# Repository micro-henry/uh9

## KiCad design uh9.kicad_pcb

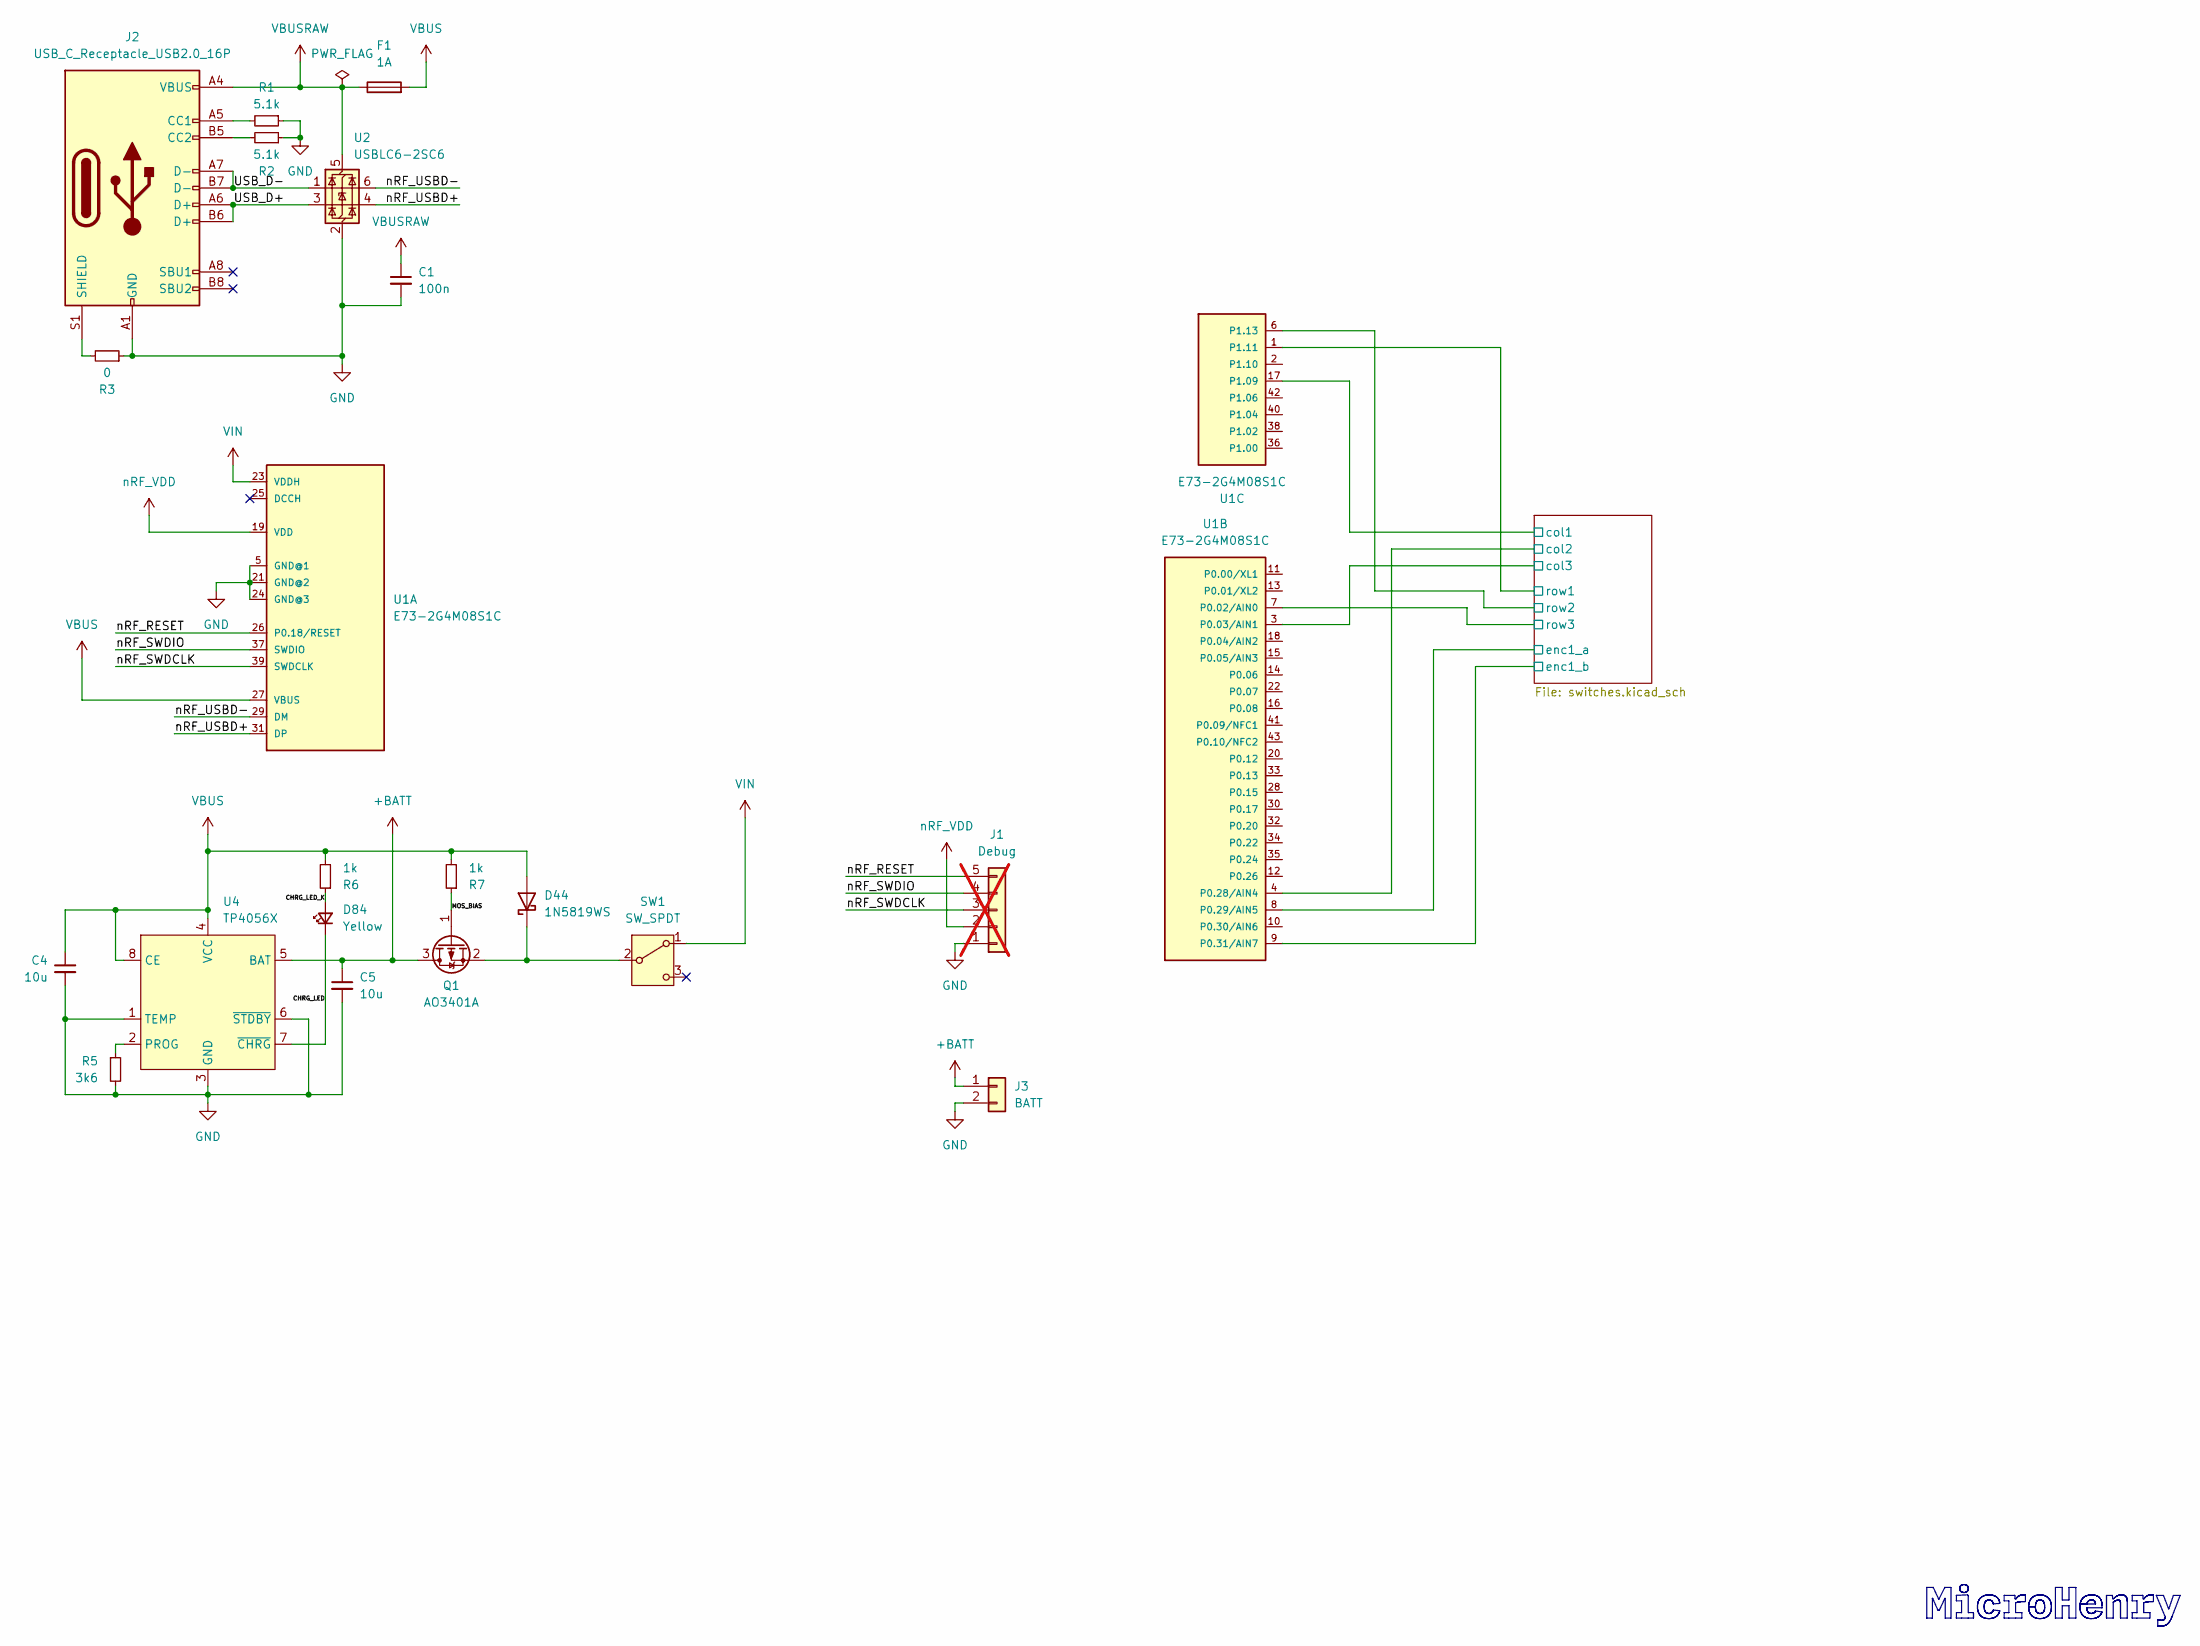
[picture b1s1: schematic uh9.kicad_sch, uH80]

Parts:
C1: 100n; C_0805_2012Metric
C4, C5: 10u; C_0805_2012Metric
D44: 1N5819WS; D_SOD-323
D84: Yellow; LED_0805_2012Metric
F1: 1A; Fuse_0805_2012Metric
J1: Debug; PinHeader_1x05_P2.00mm_Vertical; not fitted
J2: USB_C_Receptacle_USB2.0_16P; USB_C_Receptacle_HRO_TYPE-C-31-M-12
J3: BATT; CONN-SMD_2P-P2.54_MEGASTAR_ZX-XH2.54-2PWT
Q1: AO3401A; SOT-23
R1, R2: 5.1k; R_0805_2012Metric
R3: 0; R_0805_2012Metric
R5: 3k6; R_0805_2012Metric
R6, R7: 1k; R_0805_2012Metric
SW1: SW_SPDT; SW-SMD_3P-P1.50_L2.7-W6.6
U1: E73-2G4M08S1C
U2: USBLC6-2SC6; SOT-23-6
U4: TP4056X; Infineon_PG-DSO-8-27_3.9x4.9mm_EP2.65x3mm_ThermalVias

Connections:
+BATT: C5.1, J3.1, Q1.3 (D), U4.5 (BAT)
/CHRG_LED: D84.1 (K), U4.7 (~CHRG)
/CHRG_LED_K: D84.2 (A), R6.1
/MOS_BIAS: Q1.1 (G), R7.1
/USB_D+: J2.A6 (D+), J2.B6 (D+), U2.3 (I/O2)
/USB_D-: J2.A7 (D-), J2.B7 (D-), U2.1 (I/O1)
/nRF_RESET: J1.5, U1.26 (P0.18/RESET)
/nRF_SWDCLK: J1.3, U1.39 (SWDCLK)
/nRF_SWDIO: J1.4, U1.37 (SWDIO)
/nRF_USBD+: U1.31 (DP), U2.4 (I/O2)
/nRF_USBD-: U1.29 (DM), U2.6 (I/O1)
/switches/col1: U1.17 (P1.09); also elsewhere on the board
/switches/col2: U1.4 (P0.28/AIN4); also elsewhere on the board
/switches/col3: U1.3 (P0.03/AIN1); also elsewhere on the board
/switches/enc1_a: U1.8 (P0.29/AIN5); also elsewhere on the board
/switches/enc1_b: U1.9 (P0.31/AIN7); also elsewhere on the board
/switches/row1: U1.1 (P1.11); also elsewhere on the board
/switches/row2: U1.6 (P1.13); also elsewhere on the board
/switches/row3: U1.7 (P0.02/AIN0); also elsewhere on the board
GND: C1.2, C4.2, C5.2, J1.1, J2.A1 (GND), J2.A12 (GND), J2.B1 (GND), J2.B12 (GND), J3.2, R1.1, R2.1, R3.1, R5.2, U1.5 (GND@1), U1.21 (GND@2), U1.24 (GND@3), U2.2 (GND), U4.1 (TEMP), U4.3 (GND), U4.6 (~STDBY), U4.9 (GND); also elsewhere on the board
unnamed: D44.1 (K), Q1.2 (S), SW1.2 (B)
unnamed: J2.A5 (CC1), R1.2
unnamed: J2.B5 (CC2), R2.2
unnamed: J2.S1 (SHIELD), R3.2
unnamed: R5.1, U4.2 (PROG)
VBUS: C4.1, D44.2 (A), F1.2, R6.2, R7.2, U1.27 (VBUS), U4.4 (VCC), U4.8 (CE)
VBUSRAW: C1.1, F1.1, J2.A4 (VBUS), J2.A9 (VBUS), J2.B4 (VBUS), J2.B9 (VBUS), U2.5 (VBUS)
VIN: SW1.1 (A), U1.23 (VDDH)
nRF_VDD: J1.2, U1.19 (VDD)

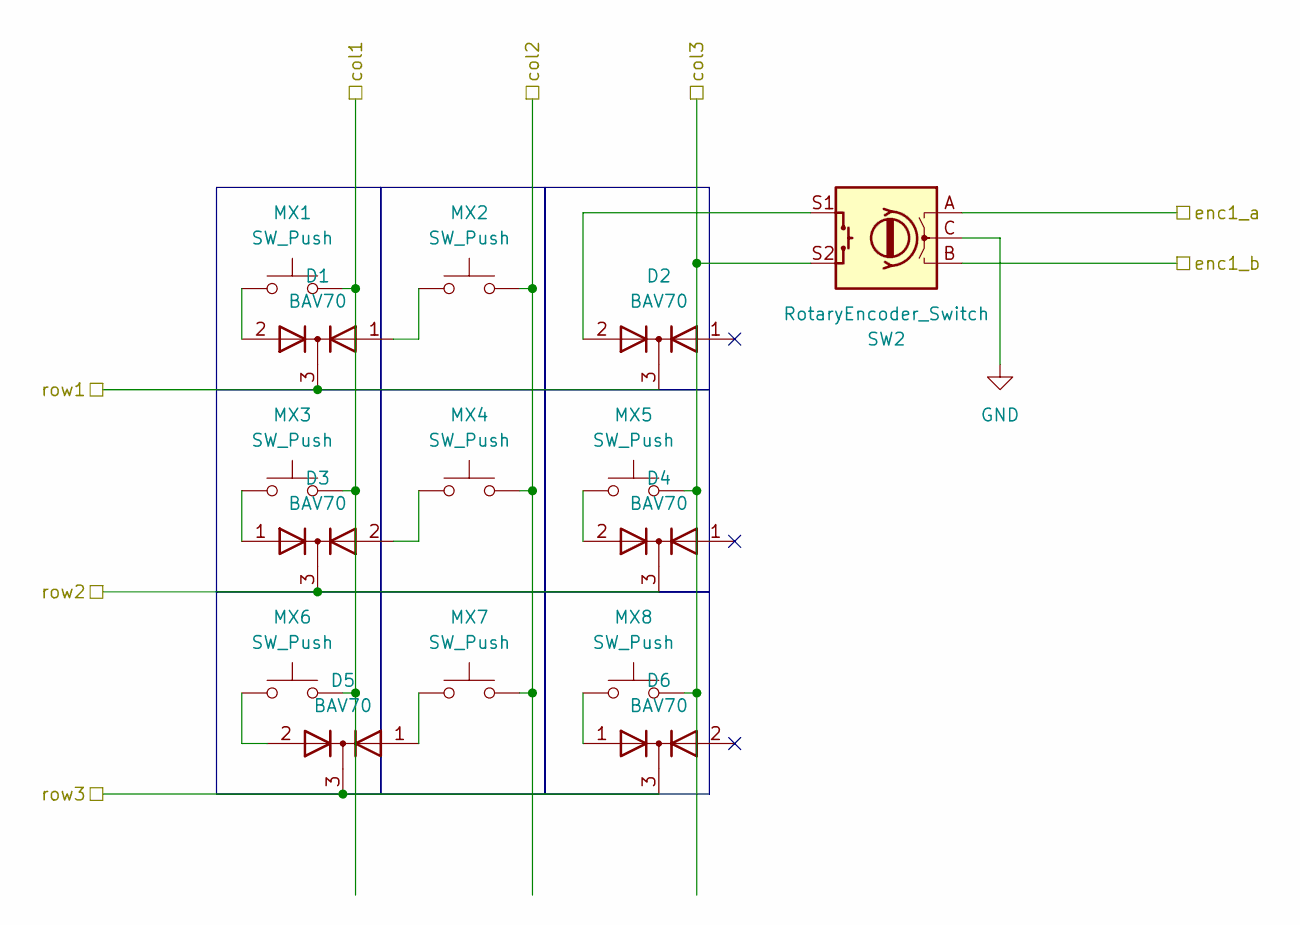
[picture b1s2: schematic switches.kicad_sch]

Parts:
D1, D2, D3, D4, D5, D6: BAV70; SOT-23
MX1, MX2, MX3, MX4, MX5, MX6, MX7, MX8: SW_Push; SW_Hotswap_Kailh_MX_1.00u
SW2: RotaryEncoder_Switch; RotaryEncoder_Alps_EC11E-Switch_Vertical_H20mm

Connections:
/switches/col1: MX1.1, MX3.2, MX6.1; also elsewhere on the board
/switches/col2: MX2.2, MX4.1, MX7.2; also elsewhere on the board
/switches/col3: MX5.1, MX8.2, SW2.S2; also elsewhere on the board
/switches/enc1_a: SW2.A; also elsewhere on the board
/switches/enc1_b: SW2.B; also elsewhere on the board
/switches/row1: D1.3 (K), D2.3 (K); also elsewhere on the board
/switches/row2: D3.3 (K), D4.3 (K); also elsewhere on the board
/switches/row3: D5.3 (K), D6.3 (K); also elsewhere on the board
GND: SW2.C; also elsewhere on the board
unnamed: D1.1 (A), MX2.1
unnamed: D1.2 (A), MX1.2
unnamed: D2.2 (A), SW2.S1
unnamed: D3.1 (A), MX3.1
unnamed: D3.2 (A), MX4.2
unnamed: D4.2 (A), MX5.2
unnamed: D5.1 (A), MX7.1
unnamed: D5.2 (A), MX6.2
unnamed: D6.1 (A), MX8.1

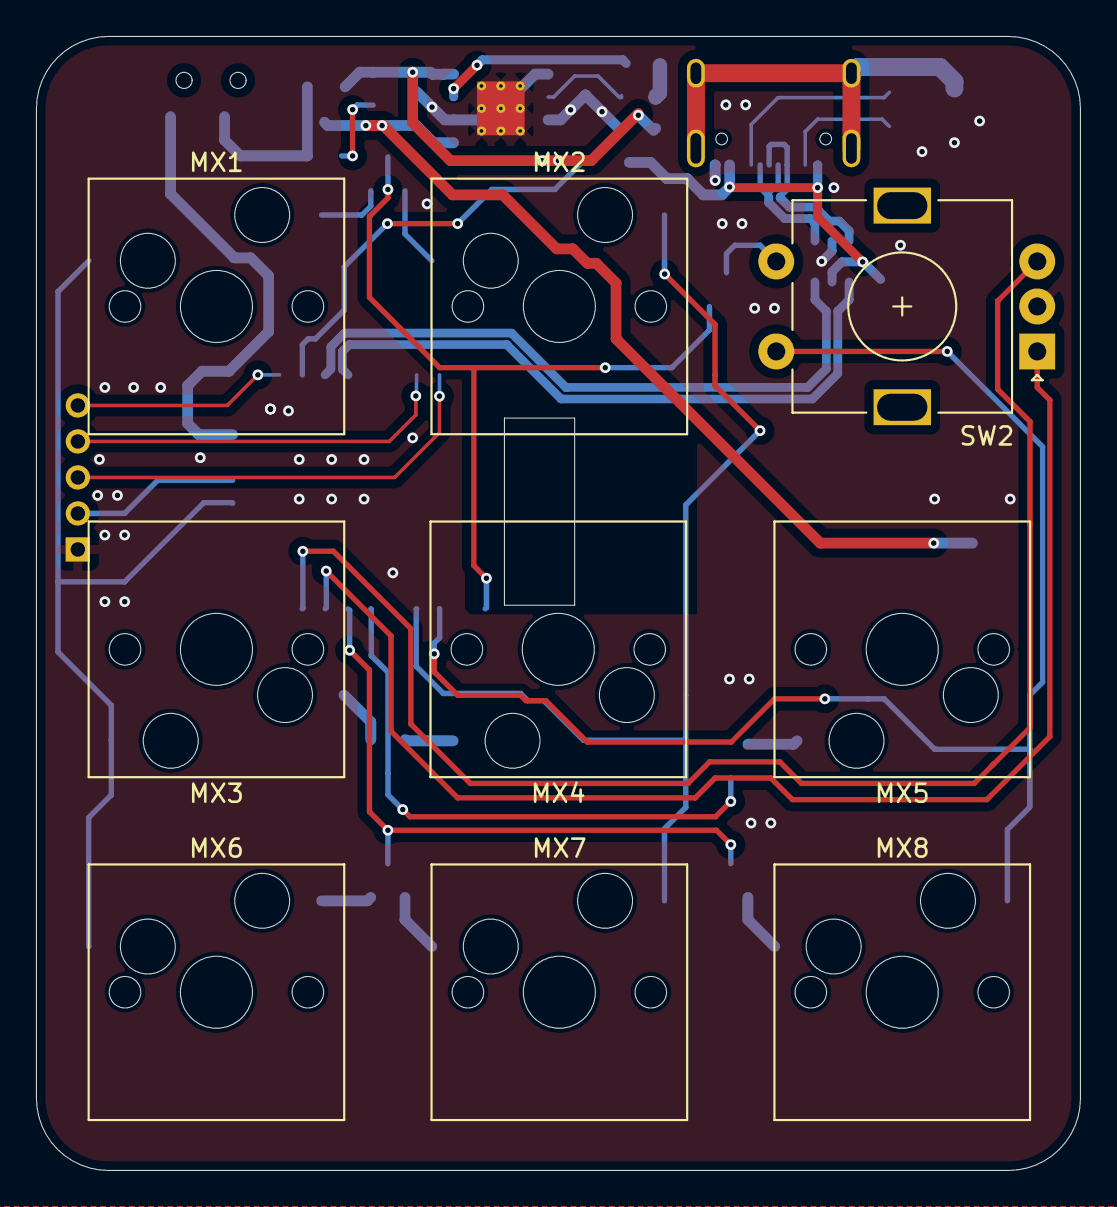
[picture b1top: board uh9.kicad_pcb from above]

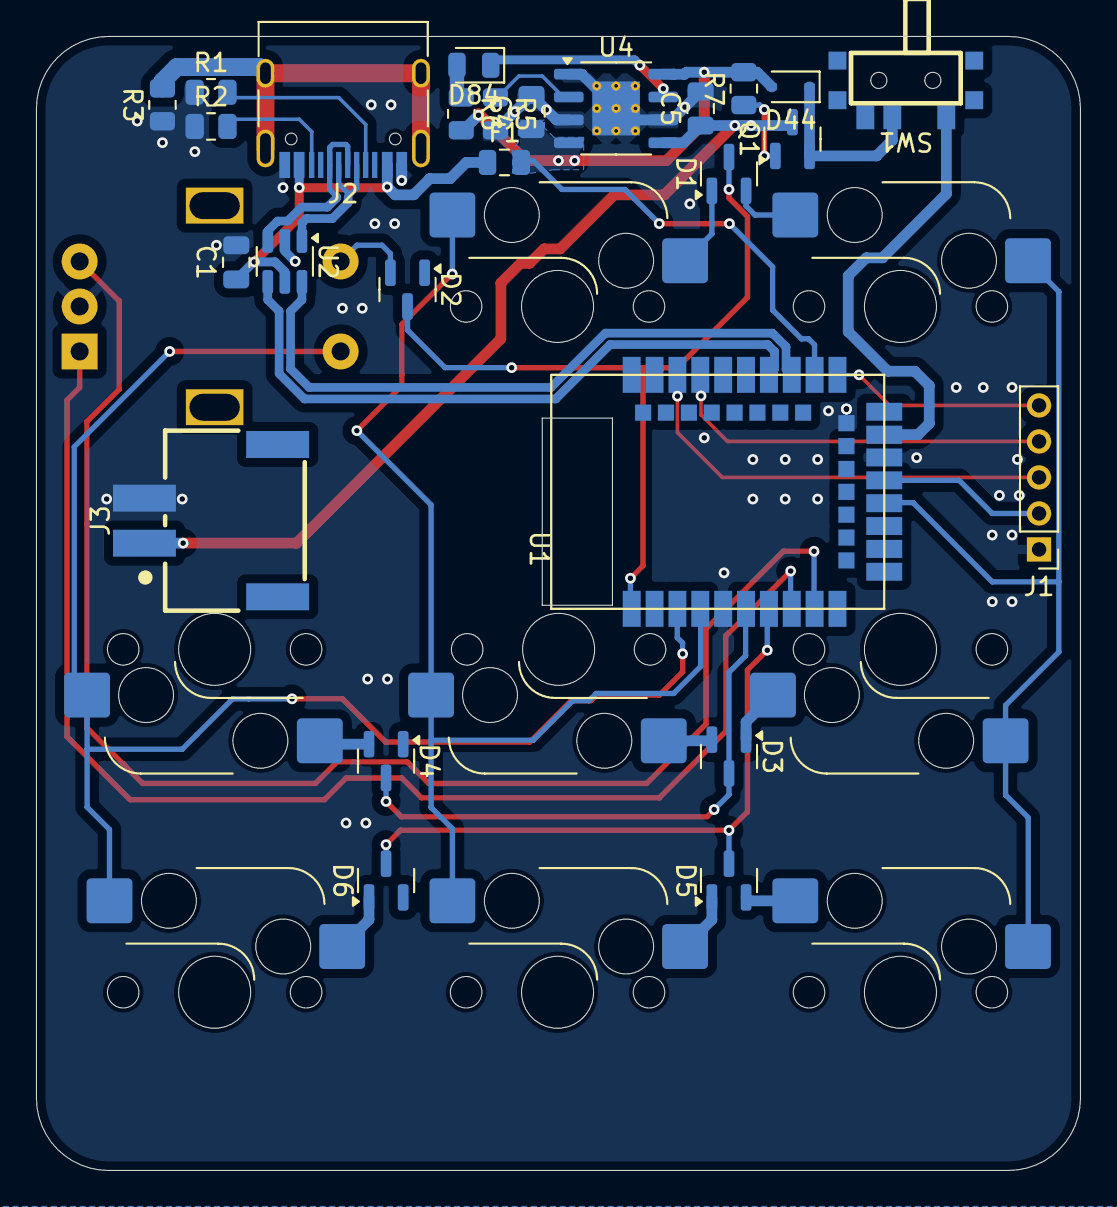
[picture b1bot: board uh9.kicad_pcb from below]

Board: 2 copper layers, 58.0 x 63.0 mm, 35 parts (26 on the bottom side), 38 nets.

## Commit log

2024-05-20 init: upload
